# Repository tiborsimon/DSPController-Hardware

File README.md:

#DSPController Hardware Designs

Schematic and PCB design in Eagle format with pregenerated gerber files.

---

### Check out the whole boundle

[DSPController Bundle](https://github.com/tiborsimon/DSPController-Bundle)

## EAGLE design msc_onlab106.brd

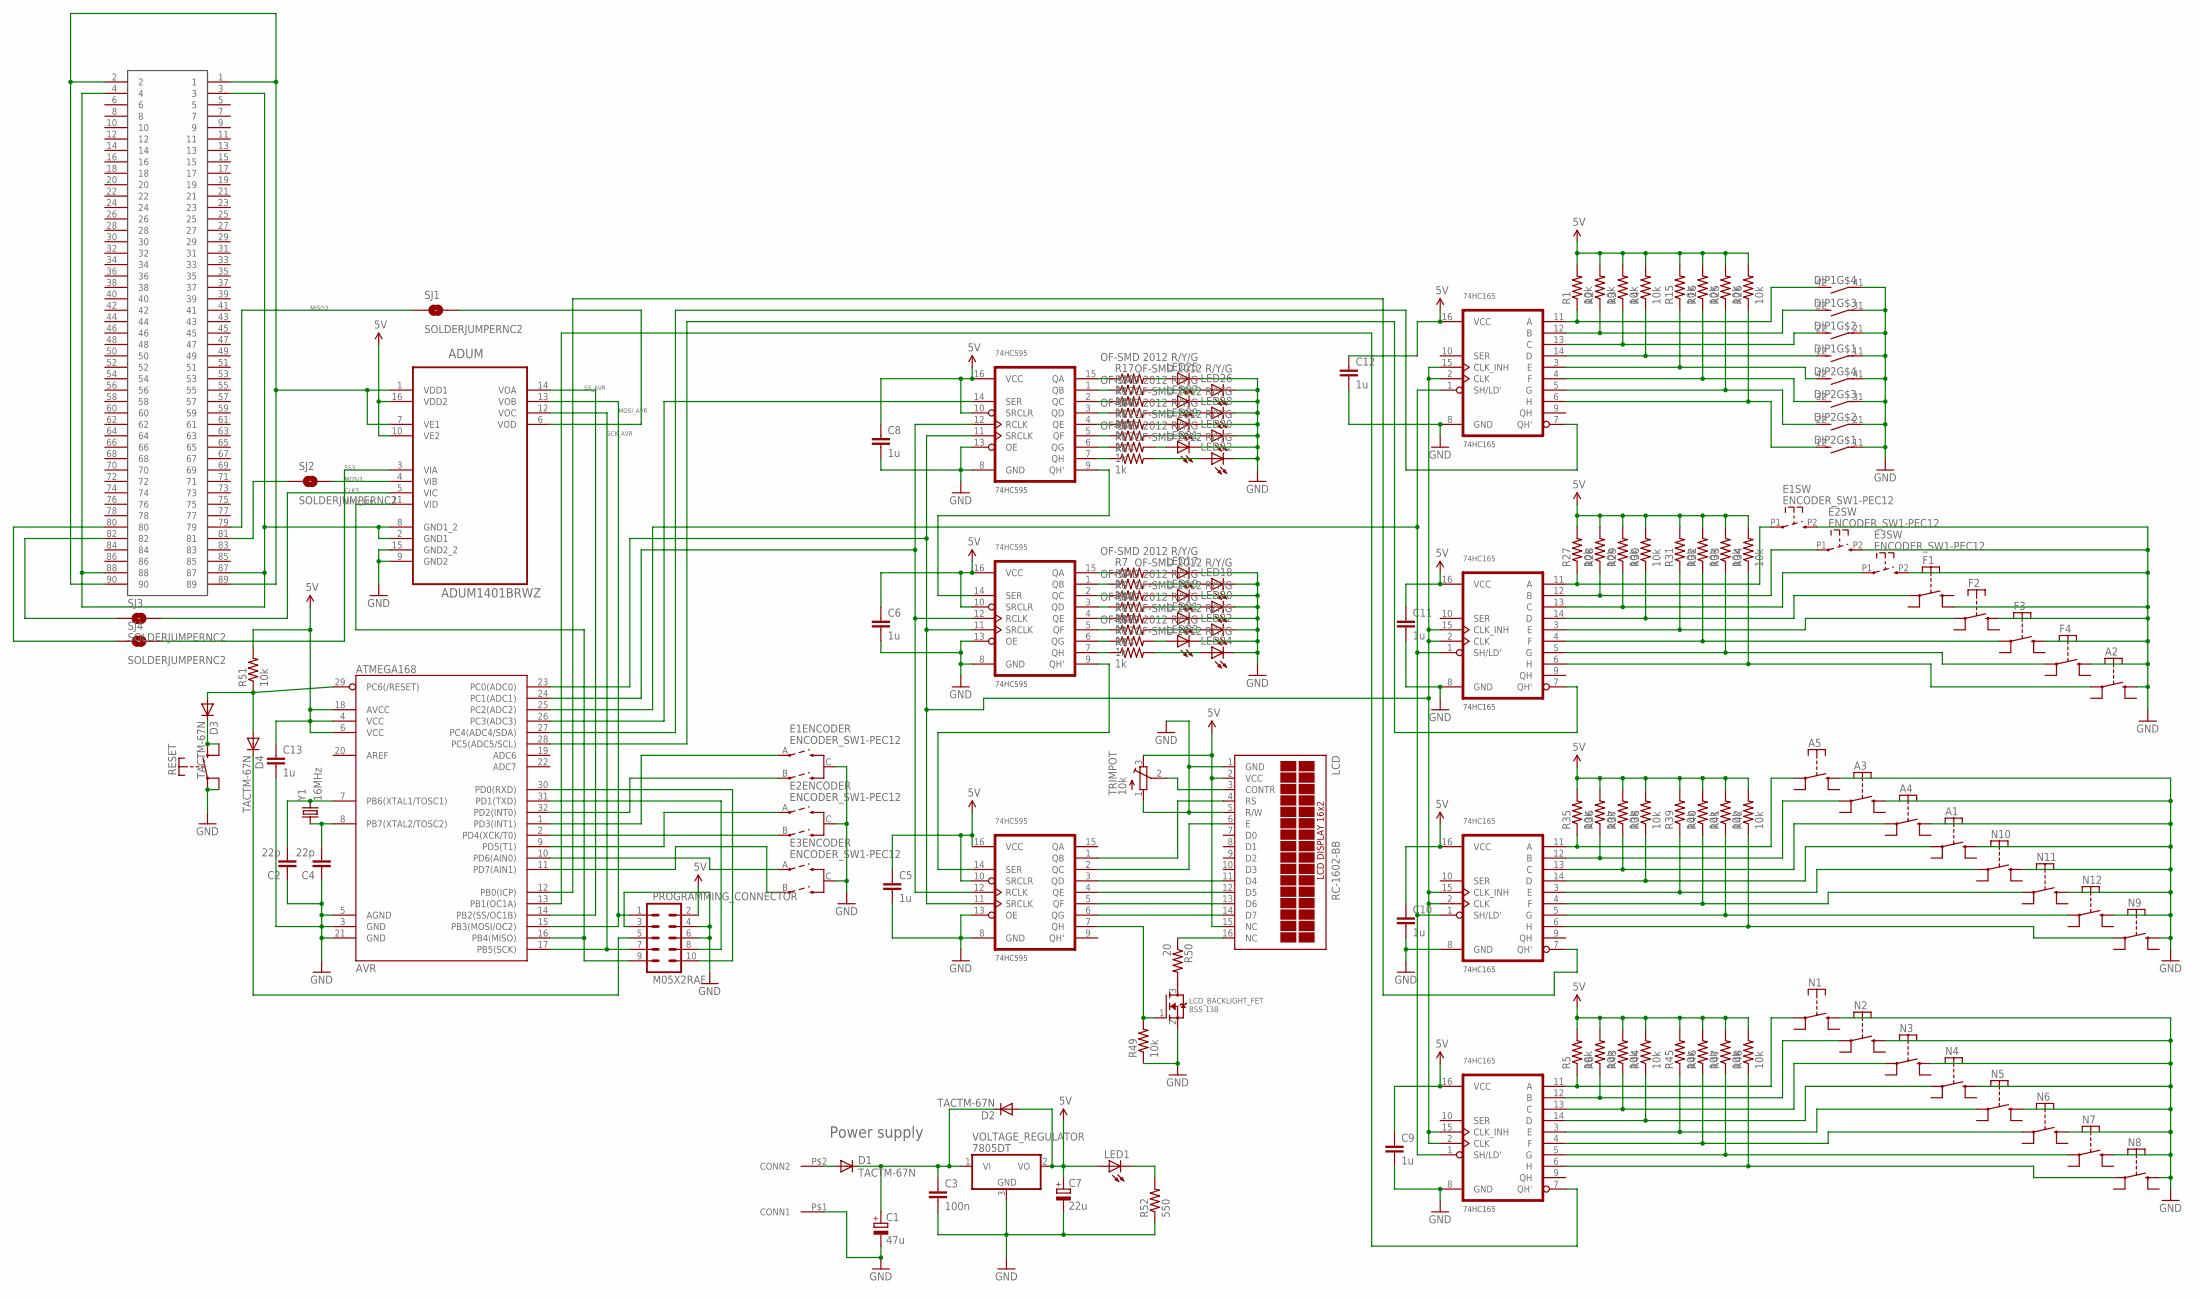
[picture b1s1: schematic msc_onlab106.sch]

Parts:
A1, A2, A3, A4, A5: TACTM-67N; SMD
ADUM: ADUM1401BRWZ; SOIC127P1032X265-16N
AVR: ATMEGA168; TQFP32-08
C1: 47u; D/7343-31W
C2, C4: 22p; 0603-CAP
C3: 100n; C0805K
C5, C6, C8, C9, C10, C11, C12, C13: 1u; 0603-CAP
C7: 22u; SMC_B
CONNECTOR: SAMTEC_TFC; SAMTEC-TFC
D1, D2, D3, D4: TACTM-67N; SMA-DIODE_ALT
DIP1, DIP2: DIP04PIANO
E1, E2, E3: ENCODER_SW1-PEC12; PEC12_INCREMENTAL_ENCODER
F1, F2, F3, F4: TACTM-67N; SMD
IN_1, IN_2, IN_3, IN_4: 74HC165; TI_PW
LCD: RC-1602-BB; TUXGR_16X2_R2
LCD_BACKLIGHT_FET: BSS 138; SOT23
LED1: LEDCHIPLED_0805; CHIPLED_0805
LED17, LED18, LED19, LED20, LED21, LED22, LED23, LED24, LED25, LED26, LED27, LED28, LED29, LED30, LED31, LED32: OF-SMD 2012 R/Y/G; CHIPLED_0805
N1, N2, N3, N4, N5, N6, N7, N8, N9, N10, N11, N12: TACTM-67N; SMD
POWER_CONNECTOR: NSL39_2_CONNECTOR
PROGRAMMING_CONNECTOR: M05X2RAF; 2X5-RAF
R1, R2, R3, R4, R5, R6, R15, R16, R25, R26, R27, R28, R29, R30, R31, R32, R33, R34, R35, R36, R37, R38, R39, R40, R41, R42, R43, R44, R45, R46, R47, R48, R49, R51: 10k; 0603-RES
R7, R8, R9, R10, R11, R12, R13, R14, R17, R18, R19, R20, R21, R22, R23, R24: 1k; 0603-RES
R50: 20; 0603-RES
R52: 550; 0603-RES
RESET: NSG 39-2; SMD
SJ1, SJ2, SJ3, SJ4: SOLDERJUMPERNC2; SJ_2S-NOTRACE
SR_OUT1, SR_OUT2, SR_OUT3: 74HC595; TI_PW
TRIMPOT: 10k; TC33X
VOLTAGE_REGULATOR: 7805DT; TO252
Y1: 16MHz; HC49UP

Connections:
3V3: ADUM.1 (VDD1), ADUM.7 (VE1), CONNECTOR.1, CONNECTOR.2, CONNECTOR.89, CONNECTOR.90
3V3_GND: ADUM.2 (GND1), ADUM.8 (GND1_2), CONNECTOR.3, CONNECTOR.4, CONNECTOR.87, CONNECTOR.88
5V: ADUM.10 (VE2), ADUM.16 (VDD2), AVR.4 (VCC), AVR.6 (VCC), AVR.18 (AVCC), C5.1, C6.1, C7.+, C8.1, C9.1, C10.1, C11.1, C12.1, C13.1, D2.A, IN_1.16 (VCC), IN_2.16 (VCC), IN_3.16 (VCC), IN_4.16 (VCC), LCD.2 (VCC), LCD.15 (NC), LED1.A, PROGRAMMING_CONNECTOR.2, R1.2, R2.2, R3.2, R4.2, R5.2, R6.2, R15.2, R16.2, R25.2, R26.2, R27.2, R28.2, R29.2, R30.2, R31.2, R32.2, R33.2, R34.2, R35.2, R36.2, R37.2, R38.2, R39.2, R40.2, R41.2, R42.2, R43.2, R44.2, R45.2, R46.2, R47.2, R48.2, R51.2, SR_OUT1.10 (SRCLR), SR_OUT1.16 (VCC), SR_OUT2.10 (SRCLR), SR_OUT2.16 (VCC), SR_OUT3.10 (SRCLR), SR_OUT3.16 (VCC), TRIMPOT.3 (E), VOLTAGE_REGULATOR.2 (VO)
CLK3: ADUM.5 (VIC), SJ3.2
GND: A1.P$4, A2.P$4, A3.P$4, A4.P$4, A5.P$4, ADUM.9 (GND2), ADUM.15 (GND2_2), AVR.3 (GND), AVR.5 (AGND), AVR.21 (GND), C1.-, C2.1, C3.2, C4.1, C5.2, C6.2, C7.-, C8.2, C9.2, C10.2, C11.2, C12.2, C13.2, DIP1.11 (1), DIP1.21 (1), DIP1.31 (1), DIP1.41 (1), DIP2.11 (1), DIP2.21 (1), DIP2.31 (1), DIP2.41 (1), E1.C, E1.P2 (2), E2.C, E2.P2 (2), E3.C, E3.P2 (2), F1.P$3, F2.P$4, F3.P$4, F4.P$4, IN_1.8 (GND), IN_2.8 (GND), IN_3.8 (GND), IN_4.8 (GND), LCD.1 (GND), LCD.5 (R/W), LCD_BACKLIGHT_FET.2 (S), LED17.C, LED18.C, LED19.C, LED20.C, LED21.C, LED22.C, LED23.C, LED24.C, LED25.C, LED26.C, LED27.C, LED28.C, LED29.C, LED30.C, LED31.C, LED32.C, N1.P$4, N2.P$4, N3.P$4, N4.P$4, N5.P$4, N6.P$4, N7.P$4, N8.P$4, N9.P$4, N10.P$4, N11.P$4, N12.P$4, POWER_CONNECTOR.P$1 (CONN1), PROGRAMMING_CONNECTOR.3, PROGRAMMING_CONNECTOR.4, PROGRAMMING_CONNECTOR.6, R49.1, R52.1, RESET.P$1, RESET.P$2, SR_OUT1.8 (GND), SR_OUT1.13 (OE), SR_OUT2.8 (GND), SR_OUT2.13 (OE), SR_OUT3.8 (GND), SR_OUT3.13 (OE), TRIMPOT.1 (A), VOLTAGE_REGULATOR.3 (GND)
IN1A: DIP1.42 (2), IN_1.11 (A), R1.1
IN1B: DIP1.32 (2), IN_1.12 (B), R2.1
IN1C: DIP1.22 (2), IN_1.13 (C), R3.1
IN1D: DIP1.12 (2), IN_1.14 (D), R4.1
IN1E: DIP2.42 (2), IN_1.3 (E), R15.1
IN1F: DIP2.32 (2), IN_1.4 (F), R16.1
IN1G: DIP2.22 (2), IN_1.5 (G), R25.1
IN1H: DIP2.12 (2), IN_1.6 (H), R26.1
IN2A: E1.P1 (1), IN_2.11 (A), R27.1
IN2B: E2.P1 (1), IN_2.12 (B), R28.1
IN2C: E3.P1 (1), IN_2.13 (C), R29.1
IN2D: F1.P$2, IN_2.14 (D), R30.1
IN2E: F2.P$2, IN_2.3 (E), R31.1
IN2F: F3.P$2, IN_2.4 (F), R32.1
IN2G: F4.P$2, IN_2.5 (G), R33.1
IN2H: A2.P$2, IN_2.6 (H), R34.1
IN3C: A4.P$2, IN_3.13 (C), R37.1
IN3D: A1.P$2, IN_3.14 (D), R38.1
IN3E: IN_3.3 (E), N10.P$2, R39.1
IN3F: IN_3.4 (F), N11.P$2, R40.1
IN3G: IN_3.5 (G), N12.P$2, R41.1
IN3H: IN_3.6 (H), N9.P$2, R42.1
IN4A: IN_4.11 (A), N1.P$2, R5.1
IN4B: IN_4.12 (B), N2.P$2, R6.1
IN4C: IN_4.13 (C), N3.P$2, R43.1
IN4D: IN_4.14 (D), N4.P$2, R44.1
IN4E: IN_4.3 (E), N5.P$2, R45.1
IN4F: IN_4.4 (F), N6.P$2, R46.1
IN4G: IN_4.5 (G), N7.P$2, R47.1
IN4H: IN_4.6 (H), N8.P$2, R48.1
IN_1: AVR.27 (PC4(ADC4/SDA)), IN_1.7 (QH')
IN_2: AVR.28 (PC5(ADC5/SCL)), IN_2.7 (QH')
IN_3: AVR.12 (PB0(ICP)), IN_3.7 (QH')
IN_4: AVR.13 (PB1(OC1A)), IN_4.7 (QH')
IN_LOAD: AVR.25 (PC2(ADC2)), IN_1.1 (SH/LD'), IN_2.1 (SH/LD'), IN_3.1 (SH/LD'), IN_4.1 (SH/LD')
IO_CLK: AVR.23 (PC0(ADC0)), IN_1.2 (CLK), IN_1.15 (CLK_INH), IN_2.2 (CLK), IN_2.15 (CLK_INH), IN_3.2 (CLK), IN_3.15 (CLK_INH), IN_4.2 (CLK), IN_4.15 (CLK_INH), SR_OUT1.11 (SRCLK), SR_OUT2.11 (SRCLK), SR_OUT3.11 (SRCLK)
MISO3: CONNECTOR.79, SJ1.1
MISO_AVR: ADUM.11 (VID), AVR.16 (PB4(MISO)), PROGRAMMING_CONNECTOR.9
MOSI3: CONNECTOR.81, SJ2.1
MOSI_AVR: ADUM.13 (VOB), AVR.15 (PB3(MOSI/OC2)), PROGRAMMING_CONNECTOR.1
unnamed: A5.P$2, IN_3.11 (A), R35.1
unnamed: A3.P$2, IN_3.12 (B), R36.1
unnamed: LCD.14 (D7), SR_OUT1.6 (QG)
unnamed: LCD.13 (D6), SR_OUT1.5 (QF)
unnamed: LCD.3 (CONTR), TRIMPOT.2 (S)
unnamed: LCD_BACKLIGHT_FET.1 (G), R49.2, SR_OUT1.7 (QH)
unnamed: LCD_BACKLIGHT_FET.3 (D), R50.2
unnamed: LCD.16 (NC), R50.1
unnamed: LCD.12 (D5), SR_OUT1.4 (QE)
unnamed: LCD.11 (D4), SR_OUT1.3 (QD)
unnamed: LCD.6 (E), SR_OUT1.2 (QC)
unnamed: D1.A, POWER_CONNECTOR.P$2 (CONN2)
unnamed: LCD.4 (RS), SR_OUT1.1 (QB)
unnamed: C1.+, C3.1, D1.C, D2.C, VOLTAGE_REGULATOR.1 (VI)
unnamed: AVR.32 (PD2(INT0)), E1.B
unnamed: AVR.8 (PB7(XTAL2/TOSC2)), C4.2, Y1.1
unnamed: CONNECTOR.82, SJ3.1
unnamed: CONNECTOR.80, SJ4.1
unnamed: AVR.7 (PB6(XTAL1/TOSC1)), C2.2, Y1.2
unnamed: AVR.1 (PD3(INT1)), E1.A
unnamed: AVR.2 (PD4(XCK/T0)), E2.B
unnamed: AVR.9 (PD5(T1)), E2.A
unnamed: LED1.C, R52.2
unnamed: ADUM.4 (VIB), SJ2.2
unnamed: AVR.10 (PD6(AIN0)), E3.A
unnamed: ADUM.6 (VOD), SJ1.2
unnamed: AVR.11 (PD7(AIN1)), E3.B
unnamed: R7.1, SR_OUT2.15 (QA)
unnamed: R8.1, SR_OUT2.1 (QB)
unnamed: R9.1, SR_OUT2.2 (QC)
unnamed: R10.1, SR_OUT2.3 (QD)
unnamed: R11.1, SR_OUT2.4 (QE)
unnamed: R12.1, SR_OUT2.5 (QF)
unnamed: R13.1, SR_OUT2.6 (QG)
unnamed: R14.1, SR_OUT2.7 (QH)
unnamed: LED17.A, R7.2
unnamed: LED18.A, R8.2
unnamed: LED19.A, R9.2
unnamed: LED20.A, R10.2
unnamed: LED21.A, R11.2
unnamed: LED22.A, R12.2
unnamed: LED23.A, R13.2
unnamed: LED24.A, R14.2
unnamed: R17.1, SR_OUT3.15 (QA)
unnamed: R18.1, SR_OUT3.1 (QB)
unnamed: R19.1, SR_OUT3.2 (QC)
unnamed: R20.1, SR_OUT3.3 (QD)
unnamed: R21.1, SR_OUT3.4 (QE)
unnamed: R22.1, SR_OUT3.5 (QF)
unnamed: R23.1, SR_OUT3.6 (QG)
unnamed: R24.1, SR_OUT3.7 (QH)
unnamed: LED25.A, R17.2
unnamed: LED26.A, R18.2
unnamed: LED27.A, R19.2
unnamed: LED28.A, R20.2
unnamed: LED29.A, R21.2
unnamed: LED30.A, R22.2
unnamed: LED31.A, R23.2
unnamed: LED32.A, R24.2
unnamed: AVR.29 (PC6(/RESET)), D3.A, D4.A, R51.1
unnamed: D3.C, RESET.P$3, RESET.P$4
OUT: AVR.26 (PC3(ADC3)), SR_OUT3.14 (SER)
OUT_DAISY: SR_OUT2.14 (SER), SR_OUT3.9 (QH')
OUT_DAISY2: SR_OUT1.14 (SER), SR_OUT2.9 (QH')
OUT_LATCH: AVR.24 (PC1(ADC1)), SR_OUT1.12 (RCLK), SR_OUT2.12 (RCLK), SR_OUT3.12 (RCLK)
RESET: D4.C, PROGRAMMING_CONNECTOR.5
RX: AVR.30 (PD0(RXD)), PROGRAMMING_CONNECTOR.10
SCK_AVR: ADUM.12 (VOC), AVR.17 (PB5(SCK)), PROGRAMMING_CONNECTOR.7
SS3: ADUM.3 (VIA), SJ4.2
SS_AVR: ADUM.14 (VOA), AVR.14 (PB2(SS/OC1B))
TX: AVR.31 (PD1(TXD)), PROGRAMMING_CONNECTOR.8

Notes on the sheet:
Power supply

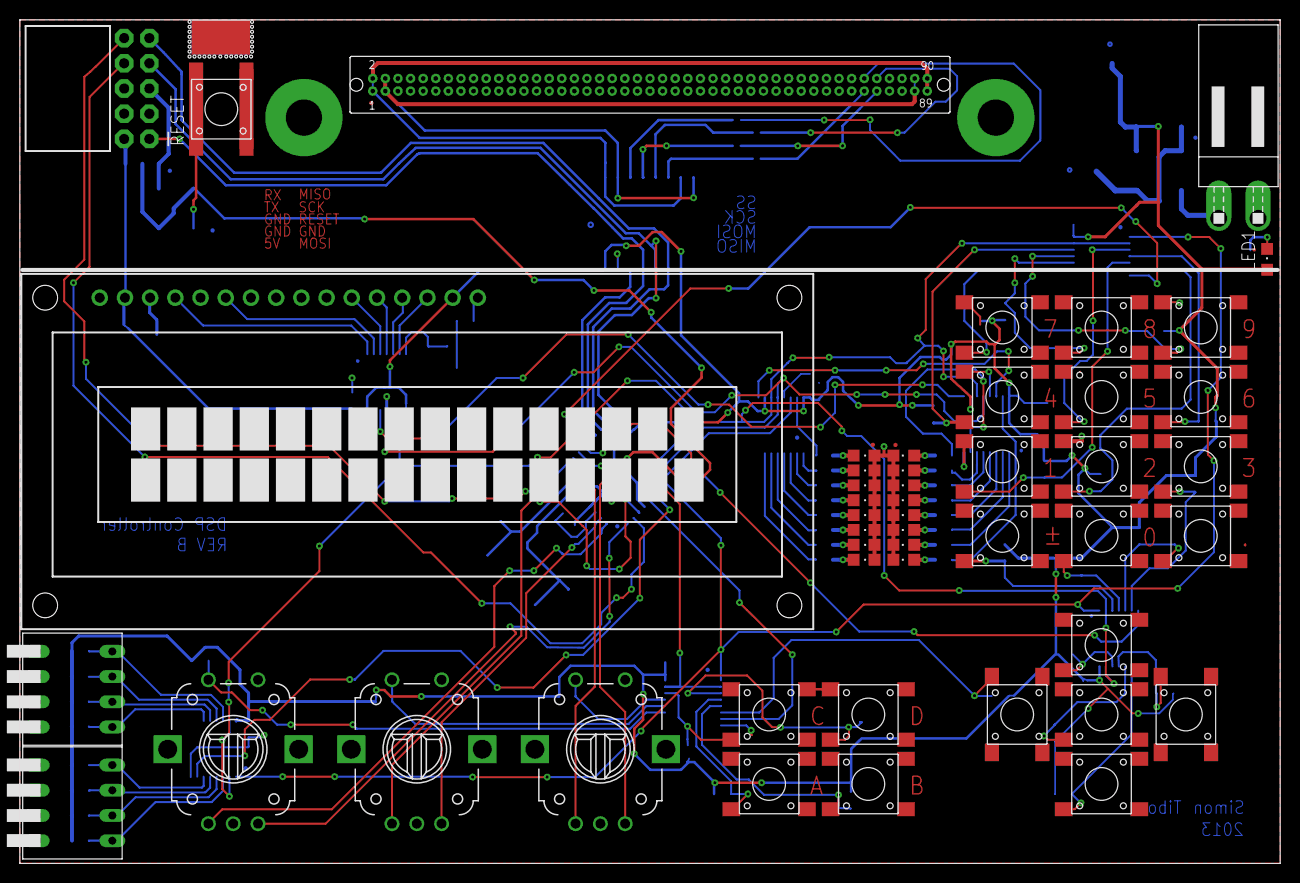
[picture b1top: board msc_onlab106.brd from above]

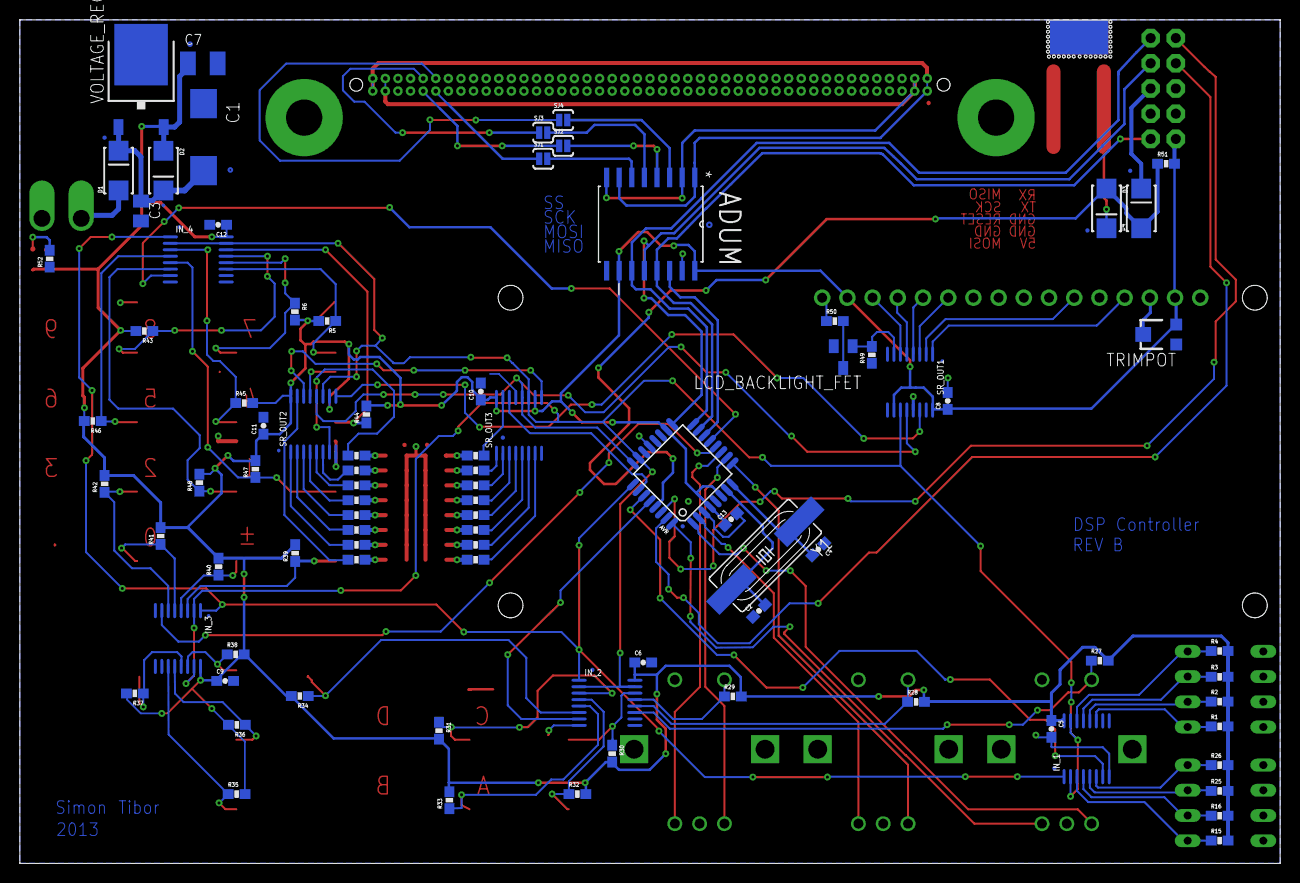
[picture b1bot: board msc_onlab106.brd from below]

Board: 2 copper layers, 127.0 x 85.0 mm, 134 parts (86 on the bottom side), 116 nets.

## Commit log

2014-01-09 Latest hardware initial commit.
2014-01-09 Values added + BOM
2014-01-09 Values added

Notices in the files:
parts and their libraries:
SparkFun: Licensing: CC v3.0 Share-Alike You are welcome to use this library for commercial purposes.
